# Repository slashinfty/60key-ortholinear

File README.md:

# 60key-ortholinear
A 5x12 ortholinear keyboard using a Raspberry Pi Pico

## Bill of Materials
* Case (see below)
* PCB (see below)
* Raspberry Pi Pico (with separate pin headers)
* 60 switches (I used Brown Gateron)
* 60 1N4148 diodes
* 60 1u keycaps

### Case
I have 3D designed a case specifically for this keyboard. It requires 4 M2.5x12mm screws.

### PCB
Gerber files have been uploaded to this repository, and a service such as JLCPCB can be used to order PCBs.

## Assembly
Complete these steps in order:
* Place the pin headers on the back, and apply solder on the front. Cut the excess flush with the PCB.
* Place diodes on the back, and apply solder on the front. Cut the excess flush with the PCB.
* Insert switches to the front of the case, mindful of orientation with the PCB.
* Place the PCB onto the switches, and apply solder on the back.
* Place the Raspberry Pi Pico on the pin headers and apply solder.
* Place the two halves of the case together and secure using screws.
* Place keycaps on switches.

## Code
First, [install CircuitPython](https://learn.adafruit.com/welcome-to-circuitpython/installing-circuitpython). Then, copy `keyboard.py` to the Raspberry Pi Pico.

The layout of the keyboard can be viewed [here](http://www.keyboard-layout-editor.com/##@_name=60key%3B&@=%0A%0A%0A%60%0A%0A%0A%0A%0A%0AEsc&=%0A%0A%0AF1%0A%0A%0A%0A%0A%0A1&=%0A%0A%0AF2%0A%0A%0A%0A%0A%0A2&=%0A%0A%0AF3%0A%0A%0A%0A%0A%0A3&=%0A%0A%0AF4%0A%0A%0A%0A%0A%0A4&=%0A%0A%0AF5%0A%0A%0A%0A%0A%0A5&=%0A%0A%0AF6%0A%0A%0A%0A%0A%0A6&=%0A%0A%0AF7%0A%0A%0A%0A%0A%0A7&=%0A%0A%0AF8%0A%0A%0A%0A%0A%0A8&=%0A%0A%0AF9%0A%0A%0A%0A%0A%0A9&=%0A%0A%0AF10%0A%0A%0A%0A%0A%0A0&=%0A%0A%0AF11%0A%0A%0A%0A%0A%0ABack%3B&@_a:7%3B&=Tab&=Q&=W&=E&=R&=T&=Y&=U&=I&=O&=P&_a:4%3B&=%0A%0A%0AF12%0A%0A%0A%0A%0A%0AEnter%3B&@_a:7%3B&=Del&=A&=S&=D&=F&=G&=H&=J&=K&=L&=%2F%3B&='%3B&@=Shift&=Z&=X&=C&=V&=B&=N&=M&_a:4%3B&=%0A%0A%0A-%0A%0A%0A%0A%0A%0A,&=%0A%0A%0A%2F=%0A%0A%0A%0A%0A%0A.&=%0A%0A%0A%5B%0A%0A%0A%0A%0A%0A%2F%2F&=%0A%0A%0A%5D%0A%0A%0A%0A%0A%0A%5C%3B&@_a:7%3B&=Prt%20Sc&=Ctrl&=Super&=Alt&=Fn%201&=&=&=Fn%202&_a:4%3B&=%0A%0A%0AH%0A%0A%0A%0A%0A%0A%2F&larr%2F%3B&=%0A%0A%0APD%0A%0A%0A%0A%0A%0A%2F&darr%2F%3B&=%0A%0A%0APU%0A%0A%0A%0A%0A%0A%2F&uarr%2F%3B&=%0A%0A%0AE%0A%0A%0A%0A%0A%0A%2F&rarr%2F).

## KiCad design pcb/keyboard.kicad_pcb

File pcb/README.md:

Raspberry Pi Pico KiCad files available [here](https://github.com/ncarandini/KiCad-RP-Pico).

Keyboard switch KiCad files available [here](https://github.com/perigoso/keyswitch-kicad-library).

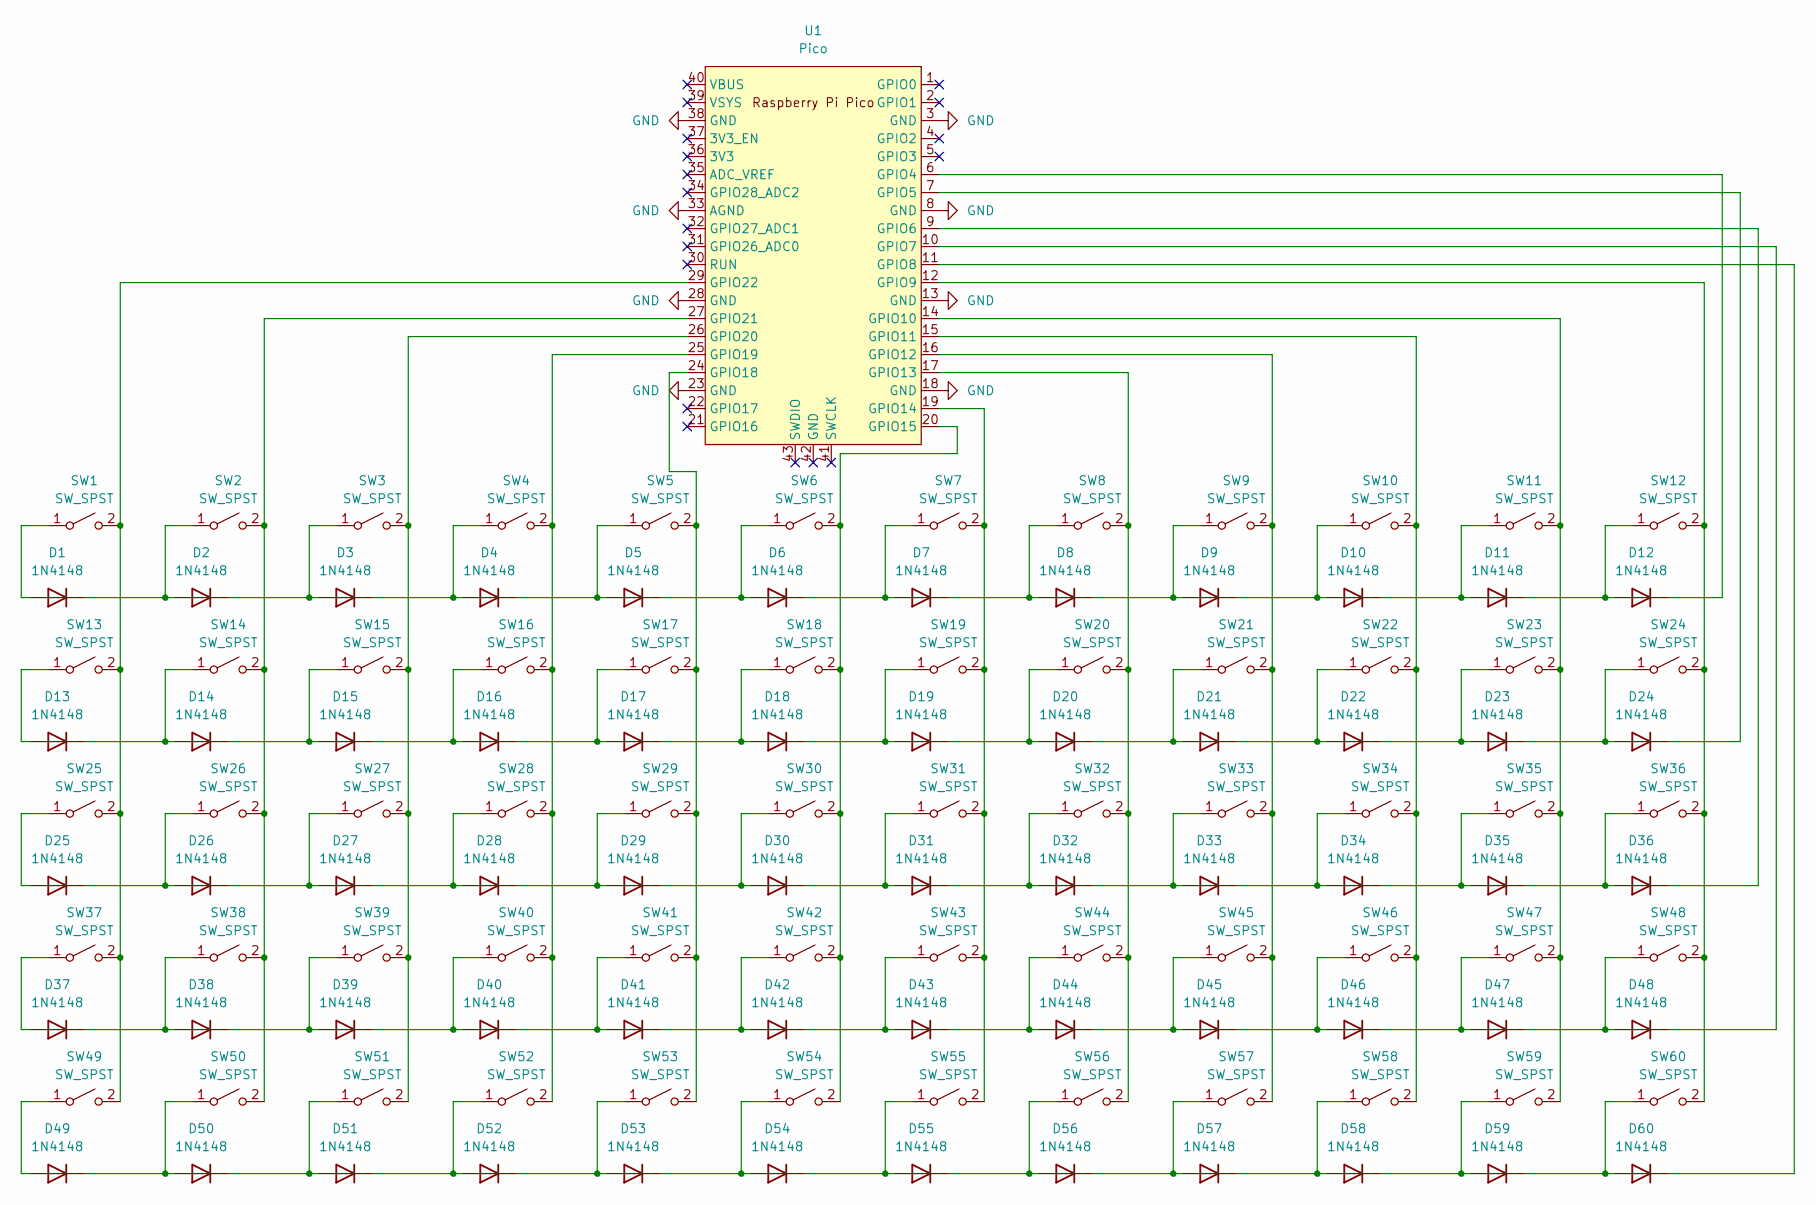
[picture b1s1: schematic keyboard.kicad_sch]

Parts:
D1, D2, D3, D4, D5, D6, D7, D8, D9, D10, D11, D12, D13, D14, D15, D16, D17, D18, D19, D20, D21, D22, D23, D24, D25, D26, D27, D28, D29, D30, D31, D32, D33, D34, D35, D36, D37, D38, D39, D40, D41, D42, D43, D44, D45, D46, D47, D48, D49, D50, D51, D52, D53, D54, D55, D56, D57, D58, D59, D60: 1N4148; D_DO-35_SOD27_P7.62mm_Horizontal
SW1, SW2, SW3, SW4, SW5, SW6, SW7, SW8, SW9, SW10, SW11, SW12, SW13, SW14, SW15, SW16, SW17, SW18, SW19, SW20, SW21, SW22, SW23, SW24, SW25, SW26, SW27, SW28, SW29, SW30, SW31, SW32, SW33, SW34, SW35, SW36, SW37, SW38, SW39, SW40, SW41, SW42, SW43, SW44, SW45, SW46, SW47, SW48, SW49, SW50, SW51, SW52, SW53, SW54, SW55, SW56, SW57, SW58, SW59, SW60: SW_SPST; SW_Cherry_MX_1.00u_Plate
U1: Pico; RPi_Pico_SMD_TH

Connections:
GND: U1.3 (GND), U1.8 (GND), U1.13 (GND), U1.18 (GND), U1.23 (GND), U1.28 (GND), U1.33 (AGND), U1.38 (GND)
unnamed: D1.1 (K), D2.2 (A), SW2.1 (A)
unnamed: D1.2 (A), SW1.1 (A)
unnamed: D2.1 (K), D3.2 (A), SW3.1 (A)
unnamed: D3.1 (K), D4.2 (A), SW4.1 (A)
unnamed: D4.1 (K), D5.2 (A), SW5.1 (A)
unnamed: D5.1 (K), D6.2 (A), SW6.1 (A)
unnamed: D6.1 (K), D7.2 (A), SW7.1 (A)
unnamed: D7.1 (K), D8.2 (A), SW8.1 (A)
unnamed: D8.1 (K), D9.2 (A), SW9.1 (A)
unnamed: D9.1 (K), D10.2 (A), SW10.1 (A)
unnamed: D10.1 (K), D11.2 (A), SW11.1 (A)
unnamed: D11.1 (K), D12.2 (A), SW12.1 (A)
unnamed: D12.1 (K), U1.6 (GPIO4)
unnamed: D13.1 (K), D14.2 (A), SW14.1 (A)
unnamed: D13.2 (A), SW13.1 (A)
unnamed: D14.1 (K), D15.2 (A), SW15.1 (A)
unnamed: D15.1 (K), D16.2 (A), SW16.1 (A)
unnamed: D16.1 (K), D17.2 (A), SW17.1 (A)
unnamed: D17.1 (K), D18.2 (A), SW18.1 (A)
unnamed: D18.1 (K), D19.2 (A), SW19.1 (A)
unnamed: D19.1 (K), D20.2 (A), SW20.1 (A)
unnamed: D20.1 (K), D21.2 (A), SW21.1 (A)
unnamed: D22.1 (K), D23.2 (A), SW23.1 (A)
unnamed: D21.1 (K), D22.2 (A), SW22.1 (A)
unnamed: D23.1 (K), D24.2 (A), SW24.1 (A)
unnamed: D24.1 (K), U1.7 (GPIO5)
unnamed: D25.1 (K), D26.2 (A), SW26.1 (A)
unnamed: D25.2 (A), SW25.1 (A)
unnamed: D26.1 (K), D27.2 (A), SW27.1 (A)
unnamed: D27.1 (K), D28.2 (A), SW28.1 (A)
unnamed: D28.1 (K), D29.2 (A), SW29.1 (A)
unnamed: D29.1 (K), D30.2 (A), SW30.1 (A)
unnamed: D30.1 (K), D31.2 (A), SW31.1 (A)
unnamed: D31.1 (K), D32.2 (A), SW32.1 (A)
unnamed: D32.1 (K), D33.2 (A), SW33.1 (A)
unnamed: D33.1 (K), D34.2 (A), SW34.1 (A)
unnamed: D34.1 (K), D35.2 (A), SW35.1 (A)
unnamed: D35.1 (K), D36.2 (A), SW36.1 (A)
unnamed: D36.1 (K), U1.9 (GPIO6)
unnamed: D37.1 (K), D38.2 (A), SW38.1 (A)
unnamed: D37.2 (A), SW37.1 (A)
unnamed: D38.1 (K), D39.2 (A), SW39.1 (A)
unnamed: D39.1 (K), D40.2 (A), SW40.1 (A)
unnamed: D40.1 (K), D41.2 (A), SW41.1 (A)
unnamed: D41.1 (K), D42.2 (A), SW42.1 (A)
unnamed: D42.1 (K), D43.2 (A), SW43.1 (A)
unnamed: D43.1 (K), D44.2 (A), SW44.1 (A)
unnamed: D44.1 (K), D45.2 (A), SW45.1 (A)
unnamed: D45.1 (K), D46.2 (A), SW46.1 (A)
unnamed: D46.1 (K), D47.2 (A), SW47.1 (A)
unnamed: D47.1 (K), D48.2 (A), SW48.1 (A)
unnamed: D48.1 (K), U1.10 (GPIO7)
unnamed: D49.1 (K), D50.2 (A), SW50.1 (A)
unnamed: D50.1 (K), D51.2 (A), SW51.1 (A)
unnamed: D51.1 (K), D52.2 (A), SW52.1 (A)
unnamed: D52.1 (K), D53.2 (A), SW53.1 (A)
unnamed: D53.1 (K), D54.2 (A), SW54.1 (A)
unnamed: D54.1 (K), D55.2 (A), SW55.1 (A)
unnamed: D55.1 (K), D56.2 (A), SW56.1 (A)
unnamed: D56.1 (K), D57.2 (A), SW57.1 (A)
unnamed: D57.1 (K), D58.2 (A), SW58.1 (A)
unnamed: D58.1 (K), D59.2 (A), SW59.1 (A)
unnamed: D59.1 (K), D60.2 (A), SW60.1 (A)
unnamed: D60.1 (K), U1.11 (GPIO8)
unnamed: SW1.2 (B), SW13.2 (B), SW25.2 (B), SW37.2 (B), SW49.2 (B), U1.29 (GPIO22)
unnamed: SW2.2 (B), SW14.2 (B), SW26.2 (B), SW38.2 (B), SW50.2 (B), U1.27 (GPIO21)
unnamed: SW3.2 (B), SW15.2 (B), SW27.2 (B), SW39.2 (B), SW51.2 (B), U1.26 (GPIO20)
unnamed: SW4.2 (B), SW16.2 (B), SW28.2 (B), SW40.2 (B), SW52.2 (B), U1.25 (GPIO19)
unnamed: SW9.2 (B), SW21.2 (B), SW33.2 (B), SW45.2 (B), SW57.2 (B), U1.16 (GPIO12)
unnamed: SW10.2 (B), SW22.2 (B), SW34.2 (B), SW46.2 (B), SW58.2 (B), U1.15 (GPIO11)
unnamed: SW11.2 (B), SW23.2 (B), SW35.2 (B), SW47.2 (B), SW59.2 (B), U1.14 (GPIO10)
unnamed: SW12.2 (B), SW24.2 (B), SW36.2 (B), SW48.2 (B), SW60.2 (B), U1.12 (GPIO9)
unnamed: SW6.2 (B), SW18.2 (B), SW30.2 (B), SW42.2 (B), SW54.2 (B), U1.20 (GPIO15)
unnamed: SW7.2 (B), SW19.2 (B), SW31.2 (B), SW43.2 (B), SW55.2 (B), U1.19 (GPIO14)
unnamed: SW8.2 (B), SW20.2 (B), SW32.2 (B), SW44.2 (B), SW56.2 (B), U1.17 (GPIO13)
unnamed: D49.2 (A), SW49.1 (A)
unnamed: SW5.2 (B), SW17.2 (B), SW29.2 (B), SW41.2 (B), SW53.2 (B), U1.24 (GPIO18)

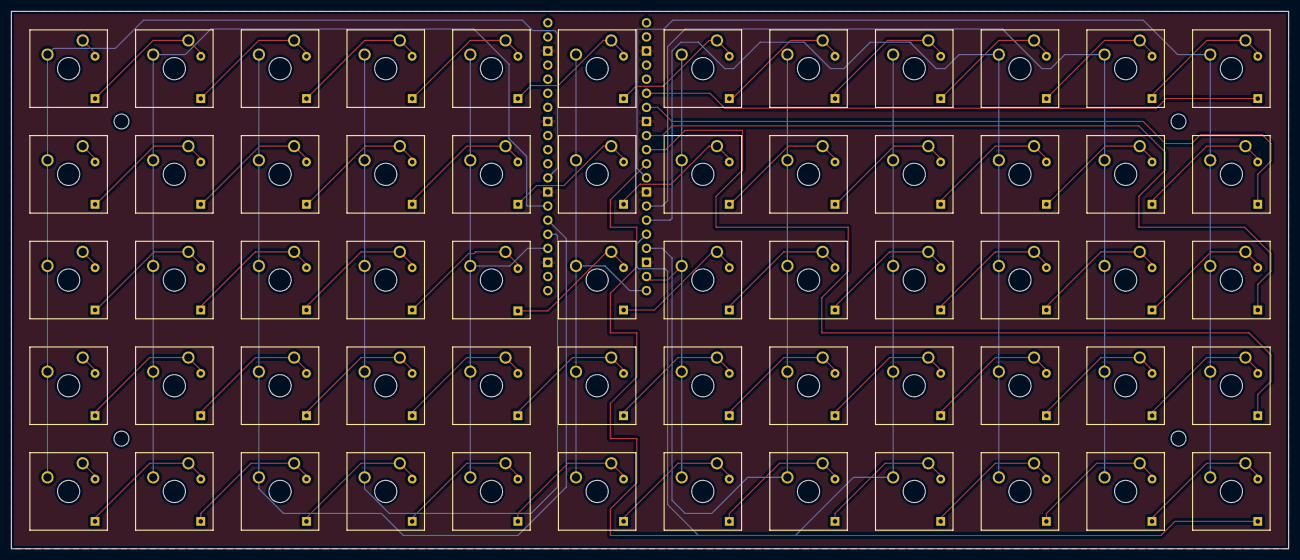
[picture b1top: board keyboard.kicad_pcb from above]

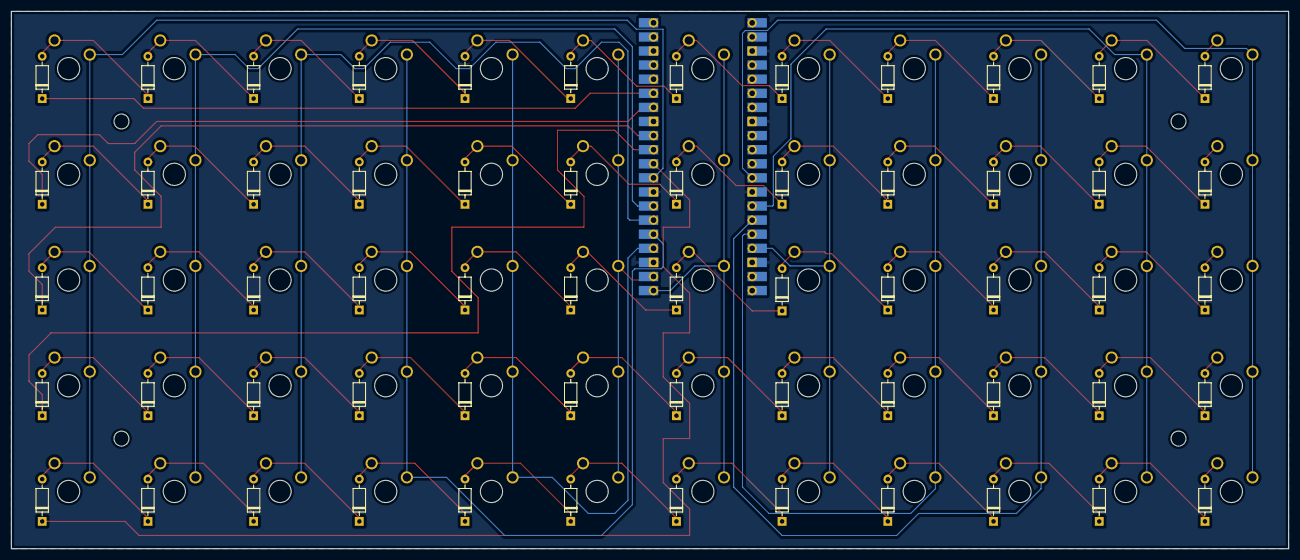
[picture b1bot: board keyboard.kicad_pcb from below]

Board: 2 copper layers, 230.2 x 96.8 mm, 121 parts (61 on the bottom side), 78 nets.

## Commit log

2022-12-28 readme
2022-12-29 pcb files
